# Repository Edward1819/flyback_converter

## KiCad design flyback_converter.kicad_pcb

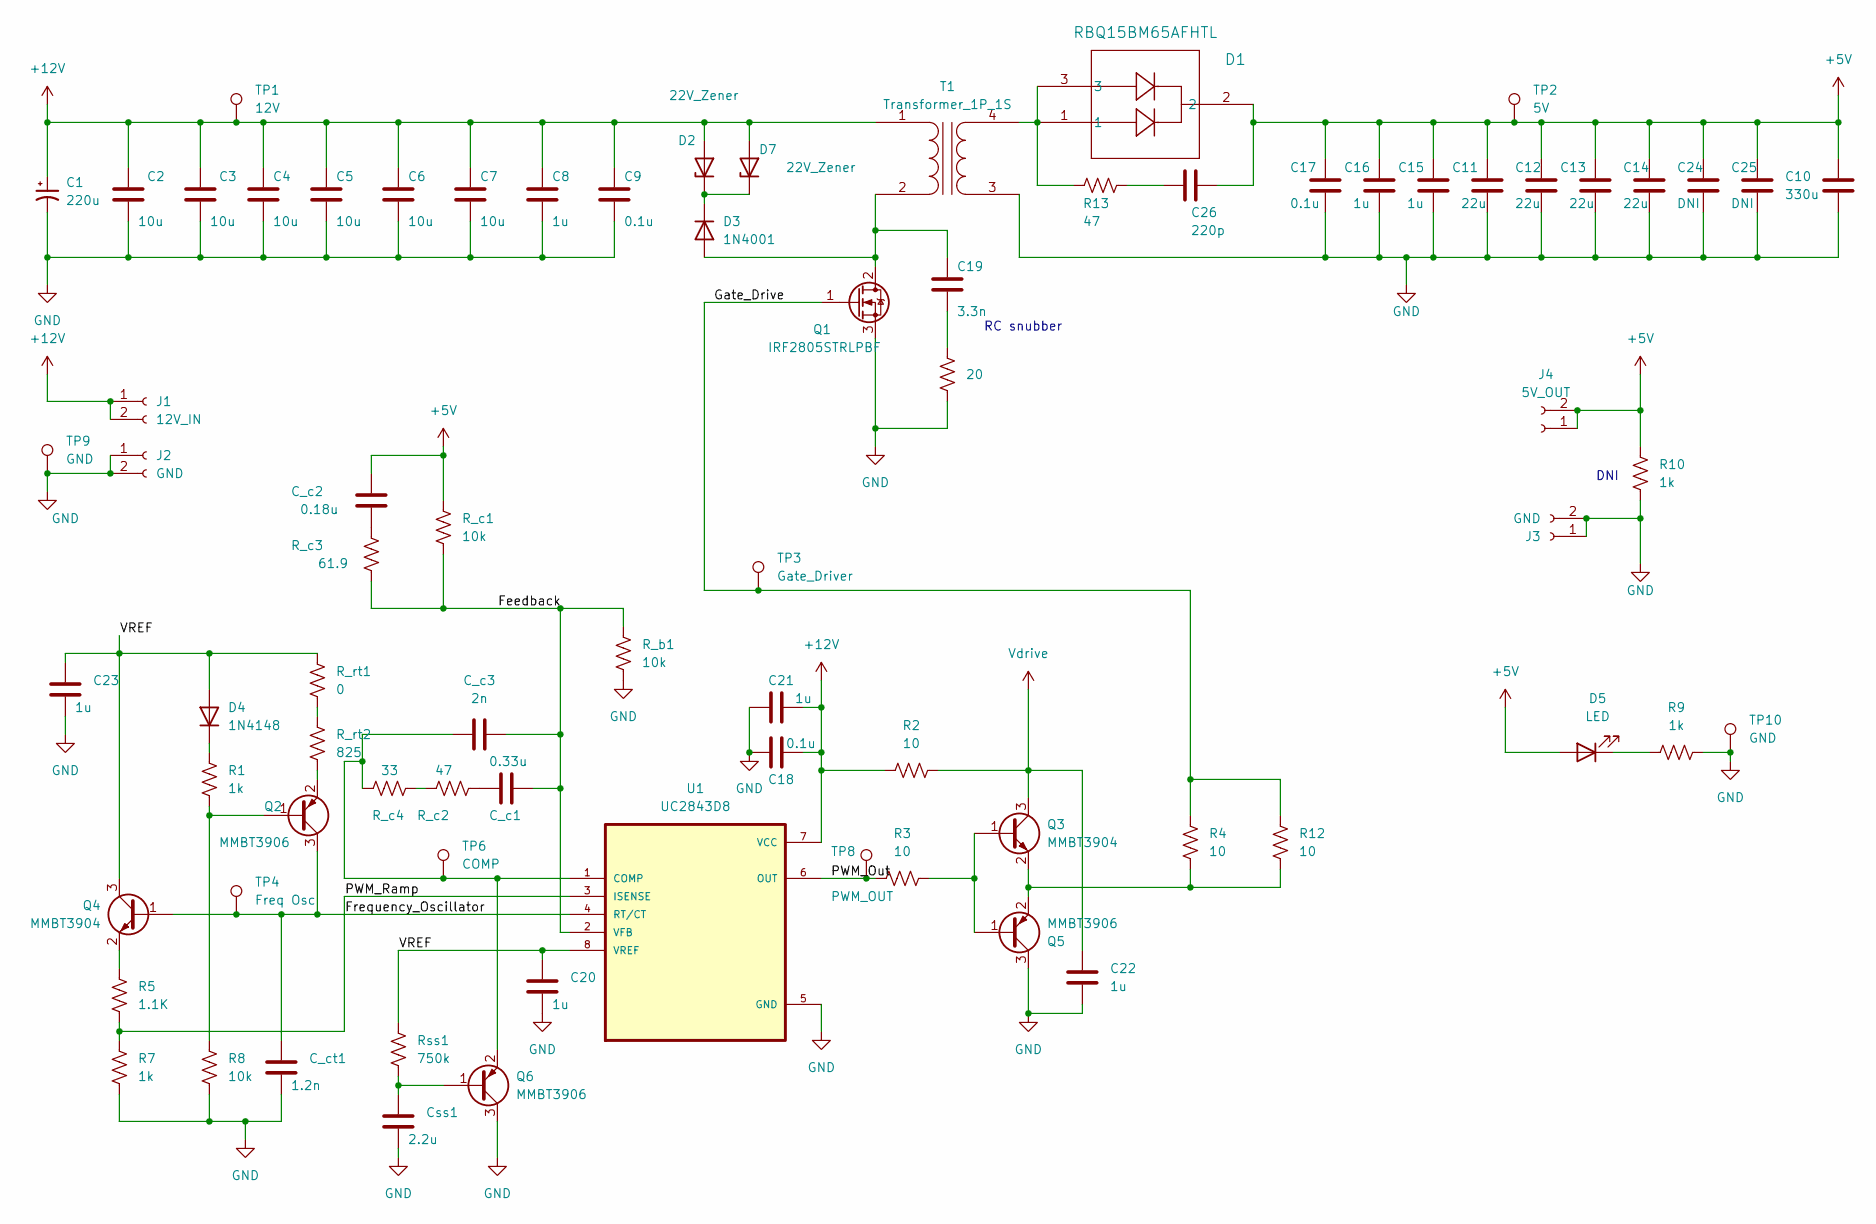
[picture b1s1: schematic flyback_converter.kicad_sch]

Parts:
C1: 220u; CP_Radial_D8.0mm_P5.00mm
C2, C3, C4, C5, C6, C7: 10u; C_1206_3216Metric_Pad1.33x1.80mm_HandSolder
C8, C15, C16, C22: 1u; C_1206_3216Metric_Pad1.33x1.80mm_HandSolder
C9, C17: 0.1u; C_1206_3216Metric_Pad1.33x1.80mm_HandSolder
C10: 330u; CP_Radial_D10.0mm_P5.00mm
C11, C12, C13, C14: 22u; C_1206_3216Metric_Pad1.33x1.80mm_HandSolder
C18: 0.1u; C_0603_1608Metric_Pad1.08x0.95mm_HandSolder
C19: 3.3n; C_0805_2012Metric_Pad1.18x1.45mm_HandSolder
C20, C21, C23: 1u; C_0603_1608Metric_Pad1.08x0.95mm_HandSolder
C24, C25: DNI; C_1206_3216Metric_Pad1.33x1.80mm_HandSolder
C26: 220p; C_0805_2012Metric_Pad1.18x1.45mm_HandSolder
C_c1: 0.33u; C_0603_1608Metric_Pad1.08x0.95mm_HandSolder
C_c2: 0.18u; C_0603_1608Metric_Pad1.08x0.95mm_HandSolder
C_c3: 2n; C_0603_1608Metric_Pad1.08x0.95mm_HandSolder
C_ct1: 1.2n; C_0603_1608Metric_Pad1.08x0.95mm_HandSolder
Css1: 2.2u; C_0603_1608Metric_Pad1.08x0.95mm_HandSolder
D1: RBQ15BM65AFHTL; DPAK228P990X239-4N
D2, D7: 22V_Zener; D_MELF
D3: 1N4001; D_SMA
D4: 1N4148; D_MELF
D5: LED; LED_1206_3216Metric_Pad1.42x1.75mm_HandSolder
J1: 12V_IN; CONN_0752-001
J2, J3: GND; CONN_0752-001
J4: 5V_OUT; CONN_0752-001
Q1: IRF2805STRLPBF; D2PAK_IRF2805_INF-M
Q2, Q5, Q6: MMBT3906; SOT-23
Q3, Q4: MMBT3904; SOT-23
R1, R7, R9: 1k; C_0603_1608Metric_Pad1.08x0.95mm_HandSolder
R2, R3, R4, R12: 10; C_0603_1608Metric_Pad1.08x0.95mm_HandSolder
R5: 1.1K; C_0603_1608Metric_Pad1.08x0.95mm_HandSolder
R6: 20; C_1206_3216Metric_Pad1.33x1.80mm_HandSolder
R8: 10k; C_0603_1608Metric_Pad1.08x0.95mm_HandSolder
R10: 1k; C_1206_3216Metric_Pad1.33x1.80mm_HandSolder
R13: 47; C_1206_3216Metric_Pad1.33x1.80mm_HandSolder
R_b1: 10k; C_0603_1608Metric_Pad1.08x0.95mm_HandSolder
R_c1: 10k; C_0603_1608Metric_Pad1.08x0.95mm_HandSolder
R_c2: 47; C_0603_1608Metric_Pad1.08x0.95mm_HandSolder
R_c3: 61.9; C_0603_1608Metric_Pad1.08x0.95mm_HandSolder
R_c4: 33; C_0603_1608Metric_Pad1.08x0.95mm_HandSolder
R_rt1: 0; C_0603_1608Metric_Pad1.08x0.95mm_HandSolder
R_rt2: 825; C_0603_1608Metric_Pad1.08x0.95mm_HandSolder
Rss1: 750k; C_0603_1608Metric_Pad1.08x0.95mm_HandSolder
T1: Transformer_1P_1S; Flyback_Xfmr
TP1: 12V; TestPoint_Pad_D1.5mm
TP2: 5V; TestPoint_Pad_D1.5mm
TP3: Gate_Driver; TestPoint_Pad_D1.5mm
TP4: Freq Osc; TestPoint_Pad_D1.5mm
TP6: COMP; TestPoint_Pad_D1.5mm
TP8: PWM_OUT; TestPoint_Pad_D1.5mm
TP9, TP10: GND; TestPoint_Pad_D1.5mm
U1: UC2843D8

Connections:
+5V: C10.1, C11.1, C12.1, C13.1, C14.1, C15.1, C16.1, C17.1, C24.1, C25.1, C26.1, C_c2.1, D1.2, D5.2 (A), J4.1, J4.2, R10.2, R_c1.1, TP2.1
+12V: C1.1, C2.1, C3.1, C4.1, C5.1, C6.1, C7.1, C8.1, C9.1, C18.1, C21.1, D2.2 (A), D7.2 (A), J1.1, J1.2, R2.1, T1.1 (AA), TP1.1, U1.7 (VCC)
/Feedback: C_c1.1, C_c3.2, R_b1.1, R_c1.2, R_c3.2, U1.2 (VFB)
/Gate_Drive: Q1.1 (G), R4.2, R12.2, TP3.1
/PWM_Out: R3.1, TP8.1, U1.6 (OUT)
/VREF: C20.1, C23.1, D4.2 (A), Q4.3 (C), R_rt1.1, Rss1.1, U1.8 (VREF)
GND: C1.2, C2.2, C3.2, C4.2, C5.2, C6.2, C7.2, C8.2, C9.2, C10.2, C11.2, C12.2, C13.2, C14.2, C15.2, C16.2, C17.2, C18.2, C20.2, C21.2, C22.2, C23.2, C24.2, C25.2, C_ct1.2, Css1.2, J2.1, J2.2, J3.1, J3.2, Q1.3 (S), Q5.3 (C), Q6.3 (C), R6.1, R7.2, R8.2, R9.2, R10.1, R_b1.2, T1.3 (SA), TP9.1, TP10.1, U1.5 (GND)
unnamed: C19.2, R6.2
unnamed: C26.2, R13.2
unnamed: C_c1.2, R_c2.1
unnamed: C_c2.2, R_c3.1
unnamed: D2.1 (K), D3.1 (K), D7.1 (K)
unnamed: C19.1, D3.2 (A), Q1.2 (D), T1.2 (AB)
unnamed: D4.1 (K), R1.1
unnamed: D5.1 (K), R9.1
unnamed: Q2.1 (B), R1.2, R8.1
unnamed: Q2.2 (E), R_rt2.2
unnamed: Q3.1 (B), Q5.1 (B), R3.2
unnamed: Q3.2 (E), Q5.2 (E), R4.1, R12.1
unnamed: Q4.2 (E), R5.1
unnamed: Css1.1, Q6.1 (B), Rss1.2
unnamed: C_c3.1, Q6.2 (E), R_c4.2, TP6.1, U1.1 (COMP)
unnamed: R_c2.2, R_c4.1
unnamed: R_rt1.2, R_rt2.1
unnamed: D1.1, D1.3, R13.1, T1.4 (SB)
Vdrive: C22.1, Q3.3 (C), R2.2

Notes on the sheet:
DNI
RC snubber

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
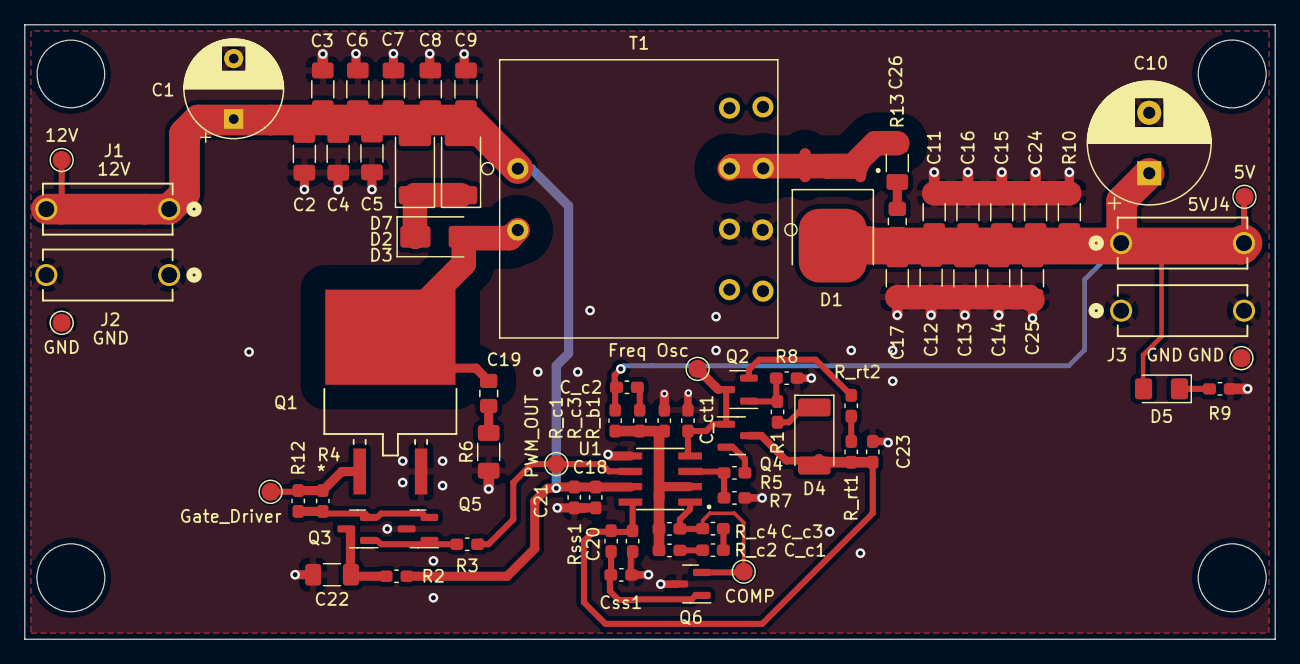
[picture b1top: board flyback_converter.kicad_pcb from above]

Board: 2 copper layers, 103.4 x 50.8 mm, 77 parts (0 on the bottom side), 28 nets.
